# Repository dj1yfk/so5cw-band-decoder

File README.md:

# Dual ICOM band decoder and antenna switch controller

WIP

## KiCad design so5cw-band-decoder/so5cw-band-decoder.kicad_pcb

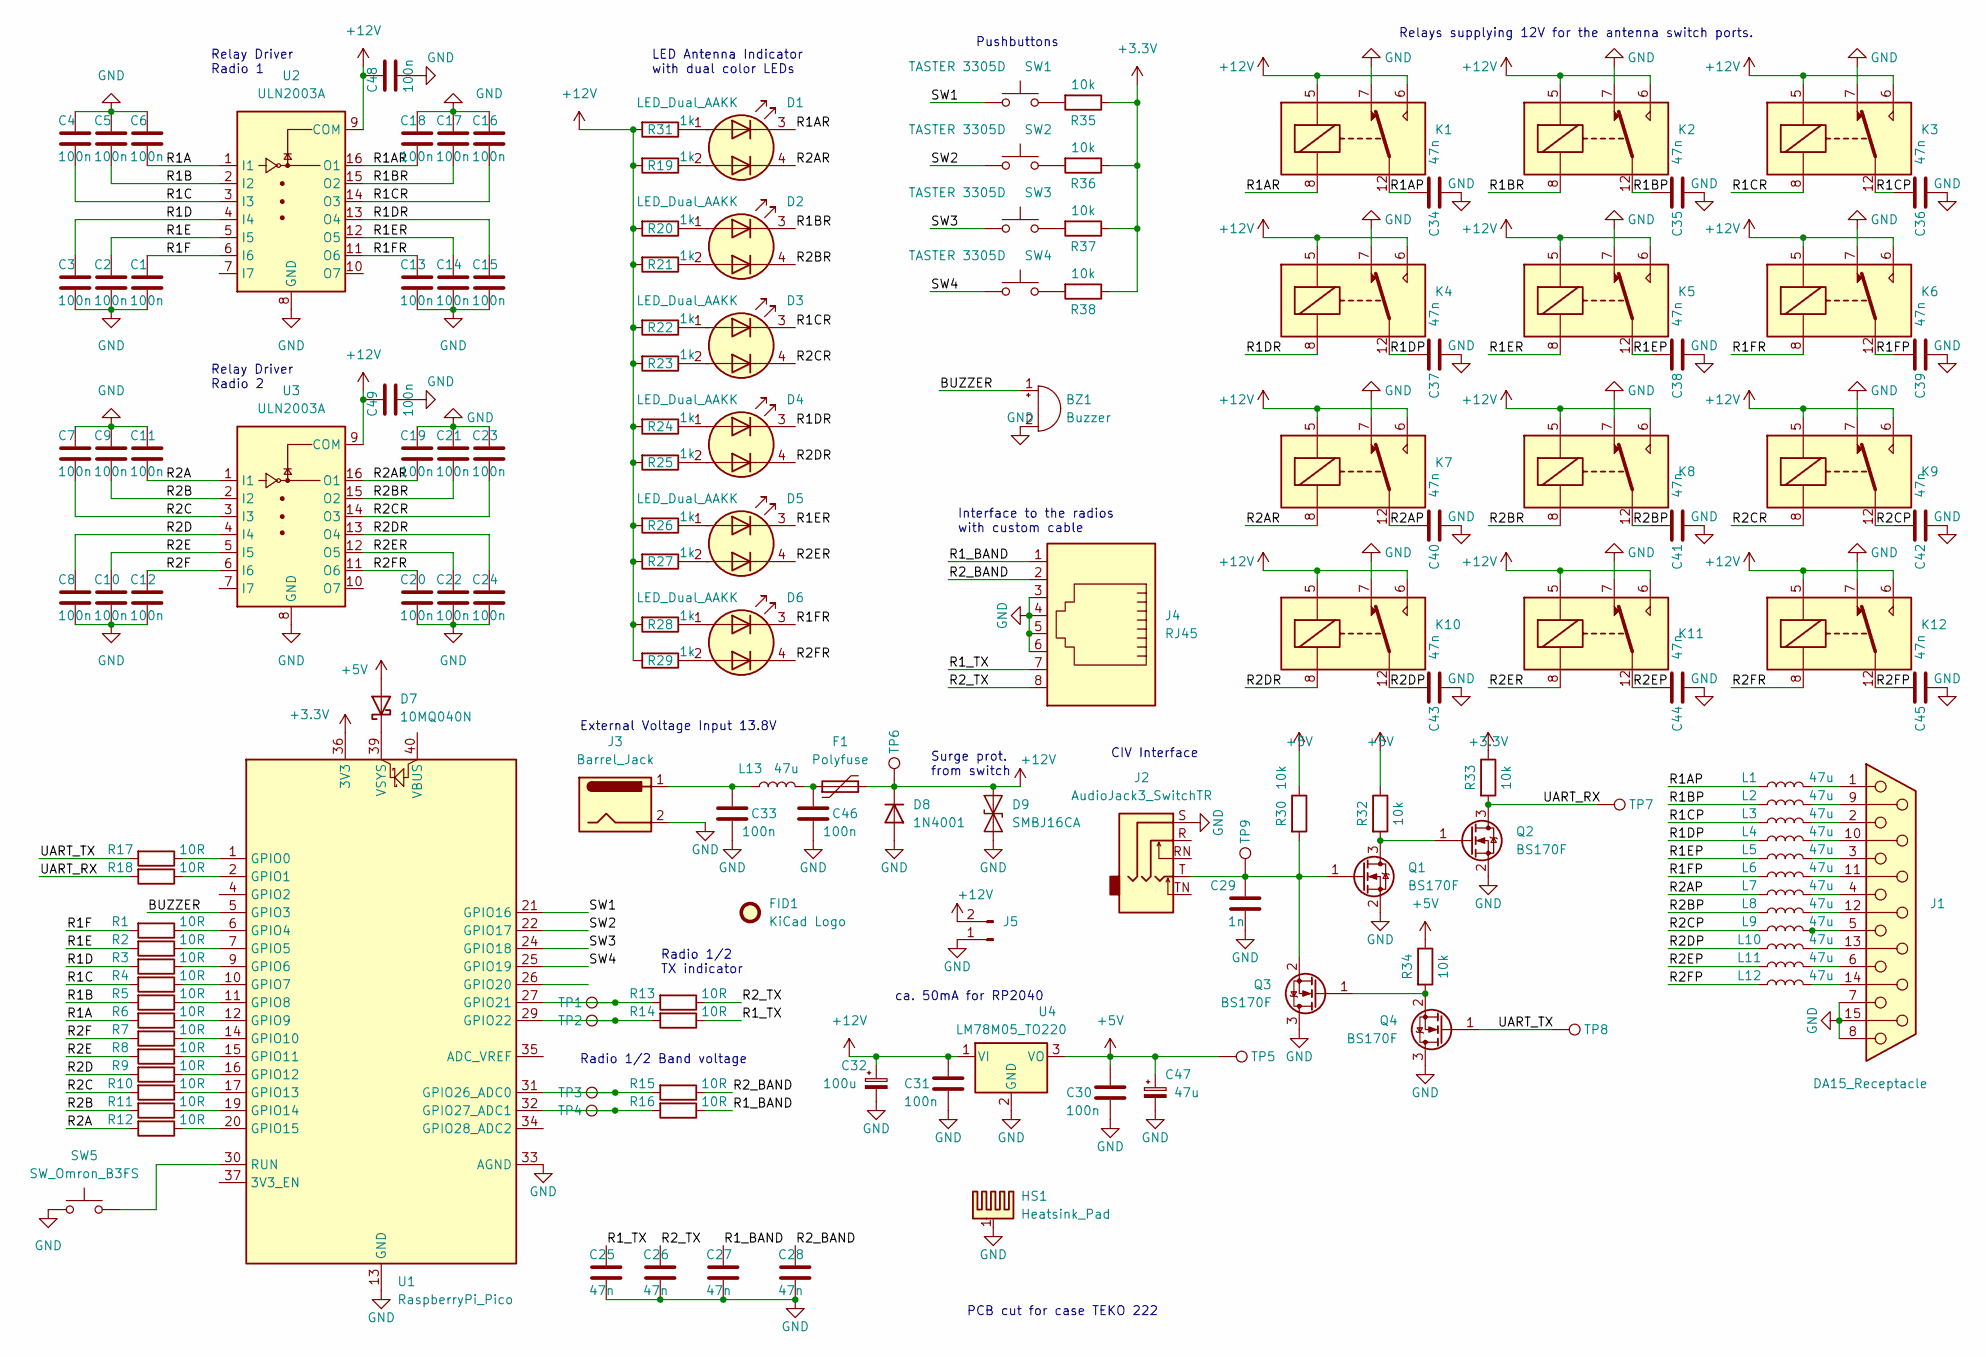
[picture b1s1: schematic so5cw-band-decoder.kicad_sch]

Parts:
BZ1: Buzzer; Buzzer_12x9.5RM6.5
C1, C2, C3, C4, C5, C6, C7, C8, C9, C10, C11, C12, C13, C14, C15, C16, C17, C18, C19, C20, C21, C22, C23, C24, C48, C49: 100n; C_0603_1608Metric_Pad1.08x0.95mm_HandSolder
C25, C26, C27, C28, C34, C35, C36, C37, C38, C39, C40, C41, C42, C43, C44, C45: 47n; C_0603_1608Metric_Pad1.08x0.95mm_HandSolder
C29: 1n; C_0603_1608Metric_Pad1.08x0.95mm_HandSolder
C30, C31, C33, C46: 100n; C_0805_2012Metric_Pad1.18x1.45mm_HandSolder
C32: 100u; CP_Elec_6.3x7.7
C47: 47u; CP_Elec_6.3x7.7
D1, D2, D3, D4, D5, D6: LED_Dual_AAKK; LED_RGB_Wuerth-PLCC4_3.2x2.8mm_150141M173100
D7: 10MQ040N; D_1812_4532Metric_Pad1.30x3.40mm_HandSolder
D8: 1N4001; D_DO-41_SOD81_P2.54mm_Vertical_AnodeUp
D9: SMBJ16CA; D_SMB_Handsoldering
F1: Polyfuse; C_1210_3225Metric_Pad1.33x2.70mm_HandSolder
FID1: KiCad Logo; KiCad-Logo2_6mm_SilkScreen
HS1: Heatsink_Pad; Heatsink_Fischer_SK104-STC-STIC_35x13mm_2xDrill2.5mm
J1: DA15_Receptacle; DSUB-15_Female_Horizontal_P2.77x2.54mm_EdgePinOffset9.40mm
J2: AudioJack3_SwitchTR; Jack_3.5mm_Ledino_KB3SPRS_Horizontal
J3: Barrel_Jack; BarrelJack_CLIFF_FC681465S_SMT_Horizontal
J4: RJ45; RJ45_Weidmueller_RJ45C5E_S1U_0.9N4N_RL
J5: Conn_01x02_Pin; PinHeader_1x02_P2.54mm_Vertical
K1, K2, K3, K4, K5, K6, K7, K8, K9, K10, K11, K12: TIANBO-HJR-4102-L; Relay_SPDT_HJR-4102
L1, L2, L3, L4, L5, L6, L7, L8, L9, L10, L11, L12, L13: 47u; L_1812_4532Metric_Pad1.30x3.40mm_HandSolder
Q1, Q2, Q3, Q4: BS170F; SOT-23W_Handsoldering
R1, R2, R3, R4, R5, R6, R7, R8, R9, R10, R11, R12, R13, R14, R15, R16, R17, R18: 10R; R_0603_1608Metric_Pad0.98x0.95mm_HandSolder
R19, R20, R21, R22, R23, R24, R25, R26, R27, R28, R29, R31: 1k; R_0603_1608Metric_Pad0.98x0.95mm_HandSolder
R30, R32, R33, R34, R35, R36, R37, R38: 10k; R_0603_1608Metric_Pad0.98x0.95mm_HandSolder
SW1, SW2, SW3, SW4: TASTER 3305D; SW_Tactile_SPST_Angled_PTS645Vx83-2LFS
SW5: SW_Omron_B3FS; SW_SPST_Omron_B3FS-100xP
TP1, TP2, TP3, TP4, TP5, TP6, TP7, TP8, TP9: TestPoint; TestPoint_THTPad_1.0x1.0mm_Drill0.5mm
U1: RaspberryPi_Pico; RaspberryPi_Pico_Common_THT
U2, U3: ULN2003A; SOIC-16W_5.3x10.2mm_P1.27mm
U4: LM78M05_TO220; TO-220-3_Vertical

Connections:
+3.3V: R33.1, R35.1, R36.1, R37.1, R38.1, U1.36 (3V3)
+5V: C30.1, C47.1, D7.2 (A), R30.1, R32.1, R34.1, TP5.1, U4.3 (VO)
+12V: C31.1, C32.1, C48.1, C49.1, D8.1 (K), D9.2 (A2), F1.2, J5.2, K1.5, K1.6, K2.5, K2.6, K3.5, K3.6, K4.5, K4.6, K5.5, K5.6, K6.5, K6.6, K7.5, K7.6, K8.5, K8.6, K9.5, K9.6, K10.5, K10.6, K11.5, K11.6, K12.5, K12.6, R19.2, R20.2, R21.2, R22.2, R23.2, R24.2, R25.2, R26.2, R27.2, R28.2, R29.2, R31.2, TP6.1, U2.9 (COM), U3.9 (COM), U4.1 (VI)
/BUZZER: BZ1.1 (+), U1.5 (GPIO3)
/R1A: C6.2, R6.2, U2.1 (I1)
/R1AP: C34.1, K1.12, L1.1
/R1AR: C18.2, D1.3 (K1), K1.8, U2.16 (O1)
/R1B: C5.2, R5.2, U2.2 (I2)
/R1BP: C35.1, K2.12, L2.1
/R1BR: C17.2, D2.3 (K1), K2.8, U2.15 (O2)
/R1C: C4.2, R4.2, U2.3 (I3)
/R1CP: C36.1, K3.12, L3.1
/R1CR: C16.2, D3.3 (K1), K3.8, U2.14 (O3)
/R1D: C3.1, R3.2, U2.4 (I4)
/R1DP: C37.1, K4.12, L4.1
/R1DR: C15.1, D4.3 (K1), K4.8, U2.13 (O4)
/R1E: C2.1, R2.2, U2.5 (I5)
/R1EP: C38.1, K5.12, L5.1
/R1ER: C14.1, D5.3 (K1), K5.8, U2.12 (O5)
/R1F: C1.1, R1.2, U2.6 (I6)
/R1FP: C39.1, K6.12, L6.1
/R1FR: C13.1, D6.3 (K1), K6.8, U2.11 (O6)
/R1_BAND: C27.1, J4.1, R16.1
/R1_TX: C25.1, J4.7, R14.1
/R2A: C11.2, R12.2, U3.1 (I1)
/R2AP: C40.1, K7.12, L7.1
/R2AR: C19.2, D1.4 (K2), K7.8, U3.16 (O1)
/R2B: C9.2, R11.2, U3.2 (I2)
/R2BP: C41.1, K8.12, L8.1
/R2BR: C21.2, D2.4 (K2), K8.8, U3.15 (O2)
/R2C: C7.2, R10.2, U3.3 (I3)
/R2CP: C42.1, K9.12, L9.1
/R2CR: C23.2, D3.4 (K2), K9.8, U3.14 (O3)
/R2D: C8.1, R9.2, U3.4 (I4)
/R2DP: C43.1, K10.12, L10.1
/R2DR: C24.1, D4.4 (K2), K10.8, U3.13 (O4)
/R2E: C10.1, R8.2, U3.5 (I5)
/R2EP: C44.1, K11.12, L11.1
/R2ER: C22.1, D5.4 (K2), K11.8, U3.12 (O5)
/R2F: C12.1, R7.2, U3.6 (I6)
/R2FP: C45.1, K12.12, L12.1
/R2FR: C20.1, D6.4 (K2), K12.8, U3.11 (O6)
/R2_BAND: C28.1, J4.2, R15.1
/R2_TX: C26.1, J4.8, R13.1
/SW1: SW1.1, U1.21 (GPIO16)
/SW2: SW2.1, U1.22 (GPIO17)
/SW3: SW3.1, U1.24 (GPIO18)
/SW4: SW4.1, U1.25 (GPIO19)
/UART_RX: Q2.3 (D), R18.2, R33.2, TP7.1
/UART_TX: Q4.1 (G), R17.2, TP8.1
GND: BZ1.2 (-), C1.2, C2.2, C3.2, C4.1, C5.1, C6.1, C7.1, C8.2, C9.1, C10.2, C11.1, C12.2, C13.2, C14.2, C15.2, C16.1, C17.1, C18.1, C19.1, C20.2, C21.1, C22.2, C23.1, C24.2, C25.2, C26.2, C27.2, C28.2, C29.2, C30.2, C31.2, C32.2, C33.2, C34.2, C35.2, C36.2, C37.2, C38.2, C39.2, C40.2, C41.2, C42.2, C43.2, C44.2, C45.2, C46.2, C47.2, C48.2, C49.2, D8.2 (A), D9.1 (A1), HS1.1, J1.7, J1.8, J1.15, J2.S, J3.2, J4.3, J4.4, J4.5, J4.6, J5.1, K1.7, K2.7, K3.7, K4.7, K5.7, K6.7, K7.7, K8.7, K9.7, K10.7, K11.7, K12.7, Q1.2 (S), Q2.2 (S), Q3.3 (D), Q4.3 (D), SW5.1, U1.3 (GND), U1.8 (GND), U1.13 (GND), U1.18 (GND), U1.23 (GND), U1.28 (GND), U1.33 (AGND), U1.38 (GND), U2.8 (GND), U3.8 (GND), U4.2 (GND)
unnamed: C33.1, J3.1, L13.1
unnamed: C46.1, F1.1, L13.2
unnamed: D1.1 (A1), R31.1
unnamed: D1.2 (A2), R19.1
unnamed: D2.1 (A1), R20.1
unnamed: D2.2 (A2), R21.1
unnamed: D3.1 (A1), R22.1
unnamed: D3.2 (A2), R23.1
unnamed: D4.1 (A1), R24.1
unnamed: D4.2 (A2), R25.1
unnamed: D5.1 (A1), R26.1
unnamed: D5.2 (A2), R27.1
unnamed: D6.1 (A1), R28.1
unnamed: D6.2 (A2), R29.1
unnamed: D7.1 (K), U1.39 (VSYS)
unnamed: J1.9, L2.2
unnamed: J1.10, L4.2
unnamed: J1.12, L8.2
unnamed: J1.13, L10.2
unnamed: J1.14, L12.2
unnamed: J1.11 (P111), L6.2
unnamed: J1.1, L1.2
unnamed: J1.2, L3.2
unnamed: J1.3, L5.2
unnamed: J1.4, L7.2
unnamed: J1.5, L9.2
unnamed: J1.6, L11.2
unnamed: Q1.3 (D), Q2.1 (G), R32.2
unnamed: C29.1, J2.T, Q1.1 (G), Q3.2 (S), R30.2, TP9.1
unnamed: Q3.1 (G), Q4.2 (S), R34.2
unnamed: R35.2, SW1.2
unnamed: R36.2, SW2.2
unnamed: R37.2, SW3.2
unnamed: R38.2, SW4.2
unnamed: R17.1, U1.1 (GPIO0)
unnamed: R18.1, U1.2 (GPIO1)
unnamed: R1.1, U1.6 (GPIO4)
unnamed: R2.1, U1.7 (GPIO5)
unnamed: R3.1, U1.9 (GPIO6)
unnamed: R4.1, U1.10 (GPIO7)
unnamed: R5.1, U1.11 (GPIO8)
unnamed: R6.1, U1.12 (GPIO9)
unnamed: R7.1, U1.14 (GPIO10)
unnamed: R8.1, U1.15 (GPIO11)
unnamed: R9.1, U1.16 (GPIO12)
unnamed: R10.1, U1.17 (GPIO13)
unnamed: R11.1, U1.19 (GPIO14)
unnamed: R12.1, U1.20 (GPIO15)
unnamed: R13.2, TP1.1, U1.27 (GPIO21)
unnamed: R14.2, TP2.1, U1.29 (GPIO22)
unnamed: R15.2, TP3.1, U1.31 (GPIO26_ADC0)
unnamed: R16.2, TP4.1, U1.32 (GPIO27_ADC1)
unnamed: SW5.2, U1.30 (RUN)

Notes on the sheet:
LED Antenna Indicator with dual color LEDs
Relay Driver Radio 2
Interface to the radios with custom cable
Radio 1/2 TX indicator
External Voltage Input 13.8V
PCB cut for case TEKO 222
Radio 1/2 Band voltage
Surge prot. from switch
Relay Driver Radio 1
Pushbuttons
ca. 50mA for RP2040
Relays supplying 12V for the antenna switch ports.
CIV Interface

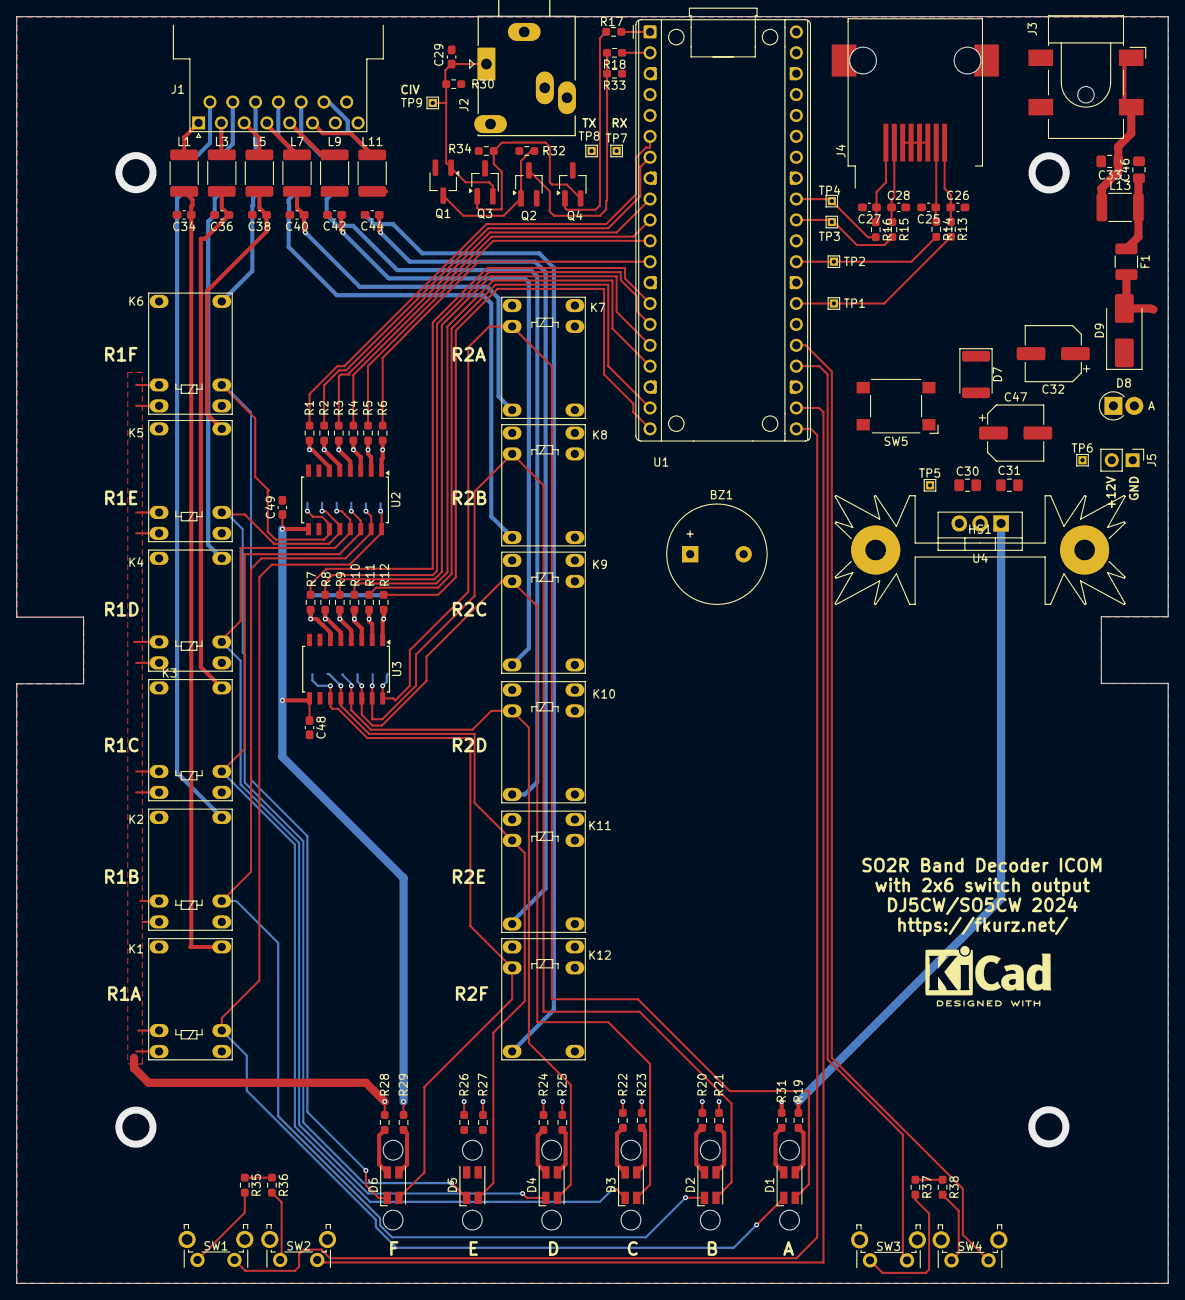
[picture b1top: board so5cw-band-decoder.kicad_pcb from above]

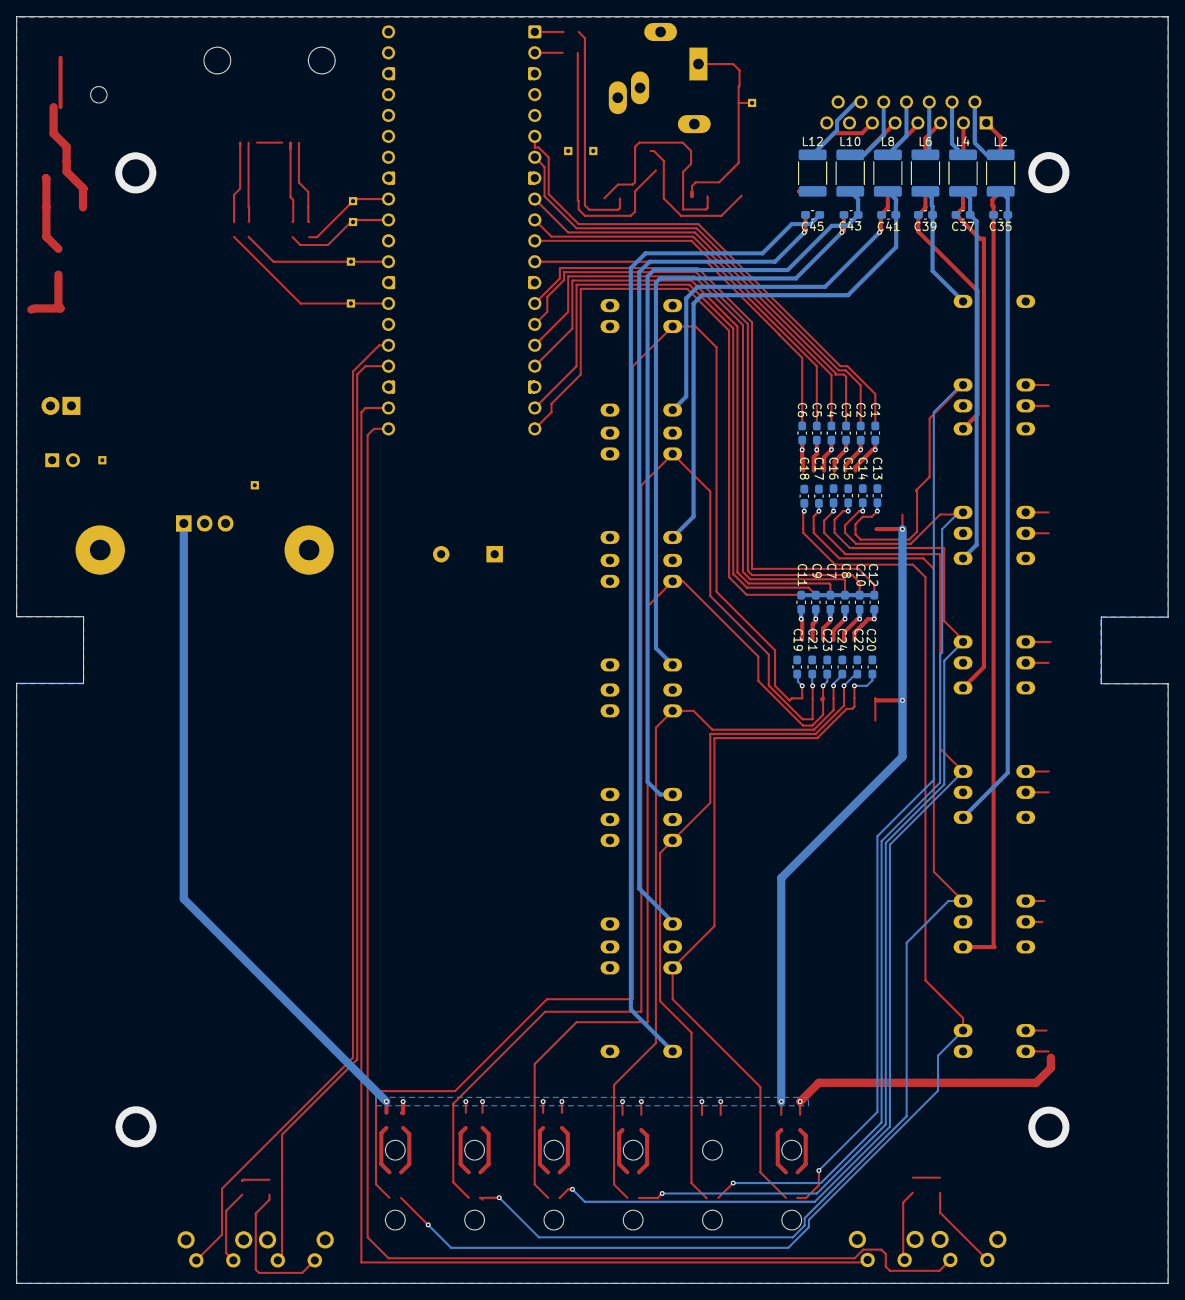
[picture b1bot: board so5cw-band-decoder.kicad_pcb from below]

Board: 2 copper layers, 140.0 x 154.0 mm, 152 parts (36 on the bottom side), 104 nets.

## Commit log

2024-04-20 Rearrange parts and route the critical connections. Needs cleanup.
2024-08-14 some more routing, add buzzer, heatsink for 5V reg, etc.
